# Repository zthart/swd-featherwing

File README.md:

# SWD Featherwing

A featherwing for Adafruit feather dev boards, including some extra prototyping space. 
This design is based on the [great tutorial](https://learn.adafruit.com/make-a-simple-debugging-featherwing-for-the-m0) available on [learn.adafruit.com](https://learn.adafruit.com/).
The repository containing the project files and information for that project is available at [mikeysklar/debug-header-feather](https://github.com/mikeysklar/debug-header-feather).
This project is licensed under the [GPL-3.0](https://www.gnu.org/licenses/gpl-3.0.en.html), as a derivative work.

## BOM

|Ref|Value|Link|
|:--|:--|:-:|
|`JST`|JST-PH 2-pin Connector|([adafruit](https://www.adafruit.com/product/1769))|
|`SWD`|SWD 10-pin Connector|([adafruit](https://www.adafruit.com/product/752))|
|`PWR`|Power LED\*|([digikey search](https://www.digikey.com/en/products/filter/led-indication-discrete/105?s=N4IgjCBcpgbFoDGUBmBDANgZwKYBoQB7KAbRAGYBOAJgBZ4BdAgBwBcoQBlVgJwEsAdgHMQAXwJhKADkoIQySOmz4ipEAAYQTEGw7d%2BwsQQC01OQt4BXFcUhkArFtHOgA))|
|`--`|12- and 16-pin Stacking Headers \*\*|([adafruit](https://www.adafruit.com/product/2830))|
|`--`|Break-apart Male Headers\*\*\*|([adafruit](https://www.adafruit.com/product/2671))|

_\* The single 0603/1608 Power indicator LED can be totally omitted if you don't want to deal with a package that small._
_Keep in mind that this LED should be mounted **upside-down** on the pads on the bottom of the board_

_\*\* These should be used on the feather that you're planning to debug, not this featherwing!_

_\*\*\* Adafruit sells a pair of 12- 16-pin male headers specifically for feathers/wings, but these pins are a bit shorter than the normal male pins that the stacking headers are designed to pair with._
_It's never a bad idea to have a few more of these on hand, so buying some extras isn't too bad!_

Depending on your debugging setup, you will need some additional cables/adapters/hardware.
If you aren't sure what components/parts you need, the original tutorial linked above contains links to all the parts you need for the [SEGGER J-Link](https://www.adafruit.com/product/1369) (edu version linked here, note the license restrictions).

## Power LED

The power LED here can be any random 0603-size LED from any retailer.
I've linked a digikey search in the BOM that filers down to the in-stock, correct package LEDs available. 
Adafruit doesn't seem to have any loose LEDs in this package (understandable, it's very small).
I just had a reel of these on hand, so I used what I had.
It would not be difficult to replace the footprint in the KiCad project. 

The idea is that this LED is installed **upside-down** on the bottom of the board, and shines through the area in the board that's clear of copper/soldermask.
You could install it right-side-up without issue - I just wanted to try out this reverse-lit PCB design.

## Where to get

This project is available on [OSH Park](https://oshpark.com/shared_projects/2qjpftBr) if you don't mind a purple solder mask. 
3 of these bad boys can be yours for about $9.
_I should note_, I have not ordered any of these boards from OSH Park, so I can't attest to how well they'll turn out.
I highly recommend buying the parts from Adafruit - the same parts can be had elsewhere, potentially even for a small discount, but Adafruit is a great company and I'm happy to support them.

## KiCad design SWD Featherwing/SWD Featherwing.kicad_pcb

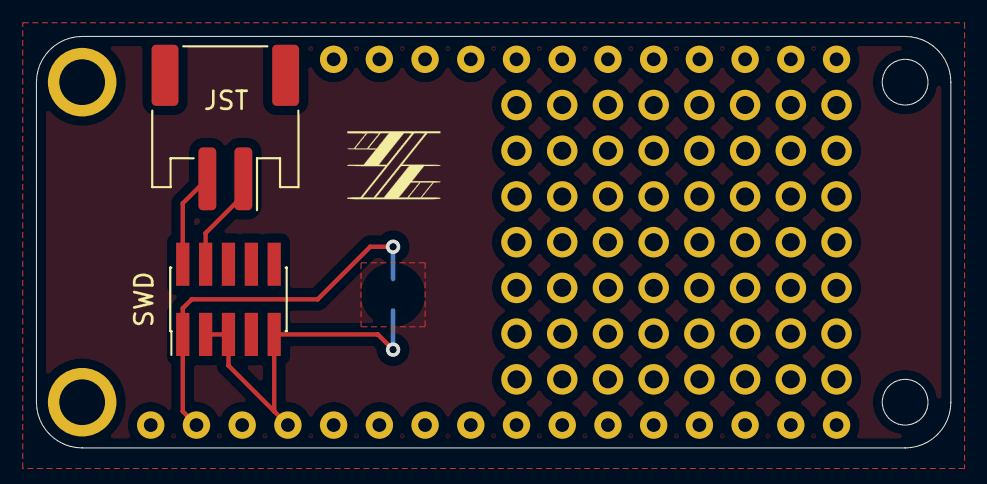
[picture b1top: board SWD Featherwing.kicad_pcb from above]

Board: 2 copper layers, 50.8 x 22.9 mm, 6 parts (1 on the bottom side), 4 nets.

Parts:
A1: Adafruit_Feather_M0_Express_No_SilkS_Drills
D1: PWR; LED_0603_1608Metric_Pad1.05x0.95mm_HandSolder
JST: Conn_01x02; JST_PH_S2B-PH-SM4-TB_1x02-1MP_P2.00mm_Horizontal
Ref**: Val**; zzzzzzzz_new_5.2x3.75mm
ST**: See_Thru_140mil
SWD: Conn_02x05_Odd_Even; PinHeader_2x05_P1.27mm_Vertical_SMD

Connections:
+3V3: A1.2, D1.2, SWD.1
/SWDCLK: JST.1, SWD.4
/SWDIO: JST.2, SWD.2
GND: A1.4, D1.1, SWD.3, SWD.5, SWD.9

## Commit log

2021-08-11 Fix bad formatting in README
2021-08-11 caveat
